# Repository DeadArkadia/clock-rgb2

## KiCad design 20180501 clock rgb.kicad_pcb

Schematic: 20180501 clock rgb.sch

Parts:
BT1: Battery CR2032; BatteryHolder_Keystone_1058_1x2032
C1, C2: 22pF; C_Rect_L4.0mm_W2.5mm_P2.50mm
C3: 1uF; C_Rect_L4.0mm_W2.5mm_P2.50mm
C4, C5, C7: 10uF; CP_Radial_D5.0mm_P2.50mm
C6, C8, C9: 1uF; CP_Radial_D5.0mm_P2.50mm
C10, C11, C12, C13: 0.1uF; CP_Radial_D5.0mm_P2.50mm
D1: APFA3010; LED_Avago_PLCC4_3.2x2.8mm_CW
D2, D3, D4, D5, D6, D7, D8, D9, D10, D11, D12, D13, D14, D15, D16, D17, D18, D19, D20, D21, D22, D23, D24, D25, D26, D27, D28, D29, D30, D31, D32, D33, D34, D35, D36, D37, D38, D39, D40, D41, D42, D43, D44, D45, D46, D47, D48, D49, D50, D51, D52, D53, D54, D55, D56, D57, D58, D59, D60, D61, D62, D63, D64, D65, D66, D67, D68, D69, D70, D71, D72, D73, D74, D75, D76, D77, D78, D79, D82, D83, D84, D85, D86, D87, D88, D91, D92, D93, D94, D95, D96, D97: LED_ARGB; LED_Avago_PLCC4_3.2x2.8mm_CW
D80, D81, D89, D90: LED; LED_D5.0mm
J1: Barrel_Jack; BARREL_JACK
J2: DB9M RS232; DSUB-9_Male_Horizontal_P2.77x2.84mm_EdgePinOffset7.70mm_Hou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
LS1: Speaker; Buzzer_15x7.5RM7.6
Q1, Q2, Q3: MMPQ2907A; SOIC-16_3.9x9.9mm_Pitch1.27mm
R1, R2, R4, R5, R7, R8, R10, R11, R13, R14, R16, R17, R19, R20, R23, R24, R26, R27, R29, R30, R32, R33, R35, R36, R38, R39, R41, R42, R51, R52, R54, R55, R57, R58, R60, R61, R63, R64, R66, R67, R69, R70, R81, R82, R84, R85, R87, R88, R90, R91, R93, R94, R96, R97, R99, R100, R111, R114, R117, R120, R123, R126, R129: 150; R_1210_3225Metric_Pad1.39x2.70mm_HandSolder
R3, R6, R9, R12, R15, R18, R21, R25, R28, R31, R34, R37, R40, R43, R53, R56, R59, R62, R65, R68, R71, R83, R86, R89, R92, R95, R98, R101: 300; R_1210_3225Metric_Pad1.39x2.70mm_HandSolder
R22: 100; R_Axial_DIN0207_L6.3mm_D2.5mm_P10.16mm_Horizontal
R44, R45, R47, R48, R49, R50, R72, R73, R74, R75, R76, R77, R78, R79, R80: 330; R_1210_3225Metric_Pad1.39x2.70mm_HandSolder
R46: 470; R_1210_3225Metric_Pad1.39x2.70mm_HandSolder
R102, R103: 2.2k; R_Axial_DIN0207_L6.3mm_D2.5mm_P10.16mm_Horizontal
R104: 10k; R_Axial_DIN0207_L6.3mm_D2.5mm_P10.16mm_Horizontal
R105, R106: 680; R_Axial_DIN0207_L6.3mm_D2.5mm_P10.16mm_Horizontal
R107, R108: 5k; R_Axial_DIN0207_L6.3mm_D2.5mm_P10.16mm_Horizontal
R109, R110, R132, R133: 10k; R_1210_3225Metric_Pad1.39x2.70mm_HandSolder
R112, R113, R115, R116, R118, R119, R121, R122, R124, R125, R127, R128, R130, R131: 100; R_1210_3225Metric_Pad1.39x2.70mm_HandSolder
RN1: 10k; R_Array_SIP4
RV1, RV2, RV3, RV4: 50k; Potentiometer_Alps_RK09K_Single_Vertical
SW1, SW2, SW3, SW4, SW5, SW6: SW_Push; SW_PUSH_6mm
U1: ATMEGA328P-PU; DIP-28_W7.62mm
U2, U3: 74164; DIP-14_W7.62mm
U5: LM7805_TO220; TO-220-3_Horizontal
U6, U7: PCA8856B; TSSOP-38_4.4x9.7mm_Pitch0.5mm
U8: DS3231-8; SOIC-8_3.9x4.9mm_Pitch1.27mm
U9: LM7812_TO220; TO-220-3_Horizontal
U10: MAX202; SOIC-16_3.9x9.9mm_Pitch1.27mm
Y1: 16MHz; Crystal_HC49-4H_Vertical

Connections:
+5V: C5.1, D89.2 (A), R102.2, R103.2, R104.2, R109.1, R110.1, RN1.1 (common), RV1.3, RV2.3, RV3.3, RV4.3, SW1.1, SW2.1, SW3.1, SW4.1, SW5.1, SW6.1, U1.7 (VCC), U1.20 (AVCC), U1.21 (AREF), U2.1 (A), U2.9 (~R), U2.14 (Vdd), U3.1 (A), U3.9 (~R), U3.14 (Vdd), U5.3 (VO), U6.2 (AD0), U6.38 (Vdd), U7.3 (AD1), U7.38 (Vdd), U8.2 (Vcc), U10.16 (VCC)
+12V: C7.1, D43.1, D44.1, D90.2 (A), Q1.10 (E4), Q1.12 (E3), Q1.14 (E2), Q1.16 (E1), Q2.10 (E4), Q2.12 (E3), Q2.14 (E2), Q3.10 (E4), Q3.12 (E3), Q3.14 (E2), Q3.16 (E1), U9.3 (VO)
/B: D1.4 (B), D2.4 (B), D3.4 (B), D4.4 (B), D5.4 (B), D6.4 (B), D7.4 (B), D8.4 (B), D9.4 (B), D10.4 (B), D11.4 (B), D12.4 (B), D13.4 (B), D14.4 (B), D15.4 (B), D16.4 (B), D17.4 (B), D18.4 (B), D19.4 (B), D20.4 (B), D21.4 (B), D22.4, D23.4, D24.4, D25.4, D26.4, D27.4, D28.4, D29.4, D30.4, D31.4, D32.4, D33.4, D34.4, D35.4, D36.4, D37.4, D38.4, D39.4, D40.4, D41.4, D42.4, D43.4, D44.4, D45.4, D46.4, D47.4, D48.4, D49.4, D50.4, D51.4, D52.4, D53.4, D54.4, D55.4, D56.4, D57.4, D58.4, D59.4, D60.4, D61.4, D62.4, D63.4, D64.4, D65.4, D66.4, D67.4, D68.4, D69.4, D70.4, D71.4, D72.4, D73.4, D74.4, D75.4, D76.4, D77.4, D78.4, D79.4, D82.4, D83.4, D84.4, D85.4, D86.4, D87.4, D88.4, R1.2, R4.2, R7.2, R10.2, R13.2, R16.2, R19.2, R23.2, R26.2, R29.2, R32.2, R35.2, R38.2, R41.2, R44.2, R51.2, R54.2, R57.2, R60.2, R63.2, R66.2, R69.2, R81.2, R84.2, R87.2, R90.2, R93.2, R96.2, R99.2
/B_COLON: R44.1, U7.33 (LED23)
/B_R1: R1.1, R23.1, R51.1, R81.1, U7.8 (LED2)
/B_R2: R4.1, R26.1, R54.1, R84.1, U7.11 (LED5)
/B_R3: R7.1, R29.1, R57.1, R87.1, U7.15 (LED8)
/B_R4: R10.1, R32.1, R60.1, R90.1, U7.19 (LED11)
/B_R5: R13.1, R35.1, R63.1, R93.1, U7.23 (LED14)
/B_R6: R16.1, R38.1, R66.1, R96.1, U7.27 (LED17)
/B_R7: R19.1, R41.1, R69.1, R99.1, U7.30 (LED20)
/DTR: C3.1, C6.1, C8.1, C9.1, U10.9 (R2OUT)
/DTR_PU: J2.4, R133.2, U10.8 (R2IN)
/G: D1.3 (G), D2.3 (G), D3.3 (G), D4.3 (G), D5.3 (G), D6.3 (G), D7.3 (G), D8.3 (G), D9.3 (G), D10.3 (G), D11.3 (G), D12.3 (G), D13.3 (G), D14.3 (G), D15.3 (G), D16.3 (G), D17.3 (G), D18.3 (G), D19.3 (G), D20.3 (G), D21.3 (G), D22.3, D23.3, D24.3, D25.3, D26.3, D27.3, D28.3, D29.3, D30.3, D31.3, D32.3, D33.3, D34.3, D35.3, D36.3, D37.3, D38.3, D39.3, D40.3, D41.3, D42.3, D43.3, D44.3, D45.3, D46.3, D47.3, D48.3, D49.3, D50.3, D51.3, D52.3, D53.3, D54.3, D55.3, D56.3, D57.3, D58.3, D59.3, D60.3, D61.3, D62.3, D63.3, D64.3, D65.3, D66.3, D67.3, D68.3, D69.3, D70.3, D71.3, D72.3, D73.3, D74.3, D75.3, D76.3, D77.3, D78.3, D79.3, D82.3, D83.3, D84.3, D85.3, D86.3, D87.3, D88.3, R2.2, R5.2, R8.2, R11.2, R14.2, R17.2, R20.2, R24.2, R27.2, R30.2, R33.2, R36.2, R39.2, R42.2, R45.2, R52.2, R55.2, R58.2, R61.2, R64.2, R67.2, R70.2, R82.2, R85.2, R88.2, R91.2, R94.2, R97.2, R100.2
/G_COLON: R45.1, U7.32 (LED22)
/G_R1: R2.1, R24.1, R52.1, R82.1, U7.7 (LED1)
/G_R2: R5.1, R27.1, R55.1, R85.1, U7.10 (LED4)
/G_R3: R8.1, R30.1, R58.1, R88.1, U7.13 (LED7)
/G_R4: R11.1, R33.1, R61.1, R91.1, U7.17 (LED10)
/G_R5: R14.1, R36.1, R64.1, R94.1, U7.22 (LED13)
/G_R6: R17.1, R39.1, R67.1, R97.1, U7.26 (LED16)
/G_R7: R20.1, R42.1, R70.1, R100.1, U7.29 (LED19)
/OE: RN1.4 (R3), U1.12 ((PCINT22/OC0A/AIN0)PD6), U6.5 (OE), U7.5 (OE)
/RXD: R80.1, U1.3 ((PCINT17/TXD)PD1), U10.11 (T1IN)
/R_COLON: R46.1, U7.31 (LED21)
/R_R1: R3.1, R25.1, R53.1, R83.1, U7.6 (LED0)
/R_R2: R6.1, R28.1, R56.1, R86.1, U7.9 (LED3)
/R_R3: R9.1, R31.1, R59.1, R89.1, U7.12 (LED6)
/R_R4: R12.1, R34.1, R62.1, R92.1, U7.16 (LED9)
/R_R5: R15.1, R37.1, R65.1, R95.1, U7.20 (LED12)
/R_R6: R18.1, R40.1, R68.1, R98.1, U7.24 (LED15)
/R_R7: R21.1, R43.1, R71.1, R101.1, U7.28 (LED18)
/SCL: RN1.2 (R1), U1.27 ((PCINT12/SDA/ADC4)PC4), U6.36 (SCL), U7.36 (SCL), U8.8 (SCL)
/SDA: RN1.3 (R2), U1.28 ((PCINT13/SCL/ADC5)PC5), U6.37 (SDA), U7.37 (SDA), U8.7 (SDA)
/STATUS1_B: R113.2, U6.8 (LED2)
/STATUS1_G: R112.2, U6.7 (LED1)
/STATUS1_R: R111.2, U6.6 (LED0)
/STATUS2_B: R116.2, U6.11 (LED5)
/STATUS2_G: R115.2, U6.10 (LED4)
/STATUS2_R: R114.2, U6.9 (LED3)
/STATUS3_B: R119.2, U6.15 (LED8)
/STATUS3_G: R118.2, U6.13 (LED7)
/STATUS3_R: R117.2, U6.12 (LED6)
/STATUS4_B: R122.2, U6.19 (LED11)
/STATUS4_G: R121.2, U6.17 (LED10)
/STATUS4_R: R120.2, U6.16 (LED9)
/STATUS5_B: R125.2, U6.23 (LED14)
/STATUS5_G: R124.2, U6.22 (LED13)
/STATUS5_R: R123.2, U6.20 (LED12)
/STATUS6_B: R128.2, U6.27 (LED17)
/STATUS6_G: R127.2, U6.26 (LED16)
/STATUS6_R: R126.2, U6.24 (LED15)
/STATUS7_B: R131.2, U6.30 (LED20)
/STATUS7_G: R130.2, U6.29 (LED19)
/STATUS7_R: R129.2, U6.28 (LED18)
/TXD: R79.1, U1.2 ((PCINT16/RXD)PD0), U10.12 (R1OUT)
/TXD_PU: J2.2, R132.2, U10.13 (R1IN)
Earth: BT1.2 (-), C1.2, C2.2, C4.2, C5.2, C7.2, C12.2, C13.1, D80.1 (K), D81.1 (K), J1.2, J1.3, J2.0 (PAD), J2.5, LS1.1, R107.1, R108.1, R132.1, R133.1, RV1.1, RV2.1, RV3.1, RV4.1, U1.8 (GND), U1.22 (GND), U2.7 (Vss), U3.7 (Vss), U5.2 (GND), U6.3 (AD1), U6.4 (AD2), U6.14 (Vss), U6.18 (Vss), U6.21 (Vss), U6.25 (Vss), U6.34 (Vss), U7.2 (AD0), U7.4 (AD2), U7.14 (Vss), U7.18 (Vss), U7.21 (Vss), U7.25 (Vss), U7.34 (Vss), U8.5 (GND), U9.2 (GND), U10.15 (GND)
unnamed: BT1.1 (+), U8.6 (VBat)
unnamed: C1.1, U1.9 ((PCINT6/XTAL1/TOSC1)PB6), Y1.1
unnamed: C2.1, U1.10 ((PCINT7/XTAL2/TOSC2)PB7), Y1.2
unnamed: C3.2, U1.1 ((PCINT14/~RESET~)PC6)
unnamed: C6.2, R104.1, U8.4 (RST)
unnamed: C8.2, R109.2, U6.35 (RESET)
unnamed: C9.2, R110.2, U7.35 (RESET)
unnamed: C10.1, U10.1 (C1+)
unnamed: C10.2, U10.3 (C1-)
unnamed: C11.1, U10.4 (C2+)
unnamed: C11.2, U10.5 (C2-)
unnamed: C12.1, U10.2 (VS+)
unnamed: C13.2, U10.6 (VS-)
unnamed: D22.1, D23.1, D24.1, D25.1, D26.1, D27.1, D28.1, D29.1, D30.1, D31.1, D32.1, D33.1, D34.1, D35.1, D36.1, D37.1, D38.1, D39.1, D40.1, D41.1, D42.1, Q1.3 (C2), Q1.4 (C2)
unnamed: D45.1, D46.1, D47.1, D48.1, D49.1, D50.1, D51.1, D52.1, D53.1, D54.1, D55.1, D56.1, D57.1, D58.1, D59.1, D60.1, D61.1, D62.1, D63.1, D64.1, D65.1, Q1.5 (C3), Q1.6 (C3)
unnamed: D66.1, D67.1, D68.1, D69.1, D70.1, D71.1, D72.1, D73.1, D74.1, D75.1, D76.1, D77.1, D78.1, D79.1, D82.1, D83.1, D84.1, D85.1, D86.1, D87.1, D88.1, Q1.7 (C4), Q1.8 (C4)
unnamed: D80.2 (A), R79.2
unnamed: D81.2 (A), R80.2
unnamed: D89.1 (K), R107.2
unnamed: D90.1 (K), R108.2
unnamed: D91.1, Q2.3 (C2), Q2.4 (C2)
unnamed: D91.2, R111.1
unnamed: D91.3, R112.1
unnamed: D91.4, R113.1
unnamed: D92.1, Q2.5 (C3), Q2.6 (C3)
unnamed: D92.2, R114.1
unnamed: D92.3, R115.1
unnamed: D92.4, R116.1
unnamed: D93.1, Q2.7 (C4), Q2.8 (C4)
unnamed: D93.2, R117.1
unnamed: D93.3, R118.1
unnamed: D93.4, R119.1
unnamed: D94.1, Q3.1 (C1), Q3.2 (C1)
unnamed: D94.2, R120.1
unnamed: D94.3, R121.1
unnamed: D94.4, R122.1
unnamed: D95.1, Q3.3 (C2), Q3.4 (C2)
unnamed: D95.2, R123.1
unnamed: D95.3, R124.1
unnamed: D95.4, R125.1
unnamed: D96.1, Q3.5 (C3), Q3.6 (C3)
unnamed: D96.2, R126.1
unnamed: D96.3, R127.1
unnamed: D96.4, R128.1
unnamed: D97.1, Q3.7 (C4), Q3.8 (C4)
unnamed: D97.2, R129.1
unnamed: D97.3, R130.1
unnamed: D97.4, R131.1
unnamed: J2.3, U10.14 (T1OUT)
unnamed: LS1.2, R22.2
unnamed: Q1.9 (B3), R50.2
unnamed: Q1.11 (B3), R49.2
unnamed: Q1.13 (B2), R48.2
unnamed: Q1.15 (B1), R47.2
unnamed: Q2.9 (B3), R76.1
unnamed: Q2.11 (B3), R77.1
unnamed: Q2.13 (B2), R78.1
unnamed: Q3.9 (B3), R72.1
unnamed: Q3.11 (B3), R73.1
unnamed: Q3.13 (B2), R74.1
unnamed: Q3.15 (B1), R75.1
unnamed: R22.1, U1.17 ((PCINT3/OC2A/MOSI)PB3)
unnamed: R47.1, U2.6 (Qd)
unnamed: R48.1, U2.5 (Qc)
unnamed: R49.1, U2.4 (Qb)
unnamed: R50.1, U2.3 (Qa)
unnamed: R72.2, U3.3 (Qa)
unnamed: R73.2, U3.4 (Qb)
unnamed: R74.2, U3.5 (Qc)
unnamed: R75.2, U3.6 (Qd)
unnamed: R76.2, U3.10 (Qe)
unnamed: R77.2, U3.11 (Qf)
unnamed: R78.2, U3.12 (Qg)
unnamed: R102.1, R105.2
unnamed: R103.1, R106.2
unnamed: R105.1, U6.1 (REXT)
unnamed: R106.1, U7.1 (REXT)
unnamed: RV1.2, U1.23 ((PCINT8/ADC0)PC0)
unnamed: RV2.2, U1.24 ((PCINT9/ADC1)PC1)
unnamed: RV3.2, U1.25 ((PCINT10/ADC2)PC2)
unnamed: RV4.2, U1.26 ((PCINT11/ADC3)PC3)
unnamed: SW1.2, U1.18 ((PCINT4/MISO)PB4)
unnamed: SW2.2, U1.19 ((PCINT5/SCK)PB5)
unnamed: SW3.2, U1.4 ((PCINT18/INT0)PD2)
unnamed: SW4.2, U1.5 ((PCINT19/OC2B/INT1)PD3)
unnamed: SW5.2, U1.6 ((PCINT20/XCK/T0)PD4)
unnamed: SW6.2, U1.11 ((PCINT21/OC0B/T1)PD5)
unnamed: U1.14 ((PCINT0/CLKO/ICP1)PB0), U2.2 (B)
unnamed: U1.15 ((PCINT1/OC1A)PB1), U2.8 (CK), U3.8 (CK)
unnamed: U1.16 ((PCINT2/OC1B/~SS~)PB2), U3.2 (B)
VCC: C4.1, J1.1, U5.1 (VI), U9.1 (VI)

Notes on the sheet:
110 1000 (68h)
001 0101 (2Ah)
000 0101 (0Ah)
TX/RX relative to PC

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
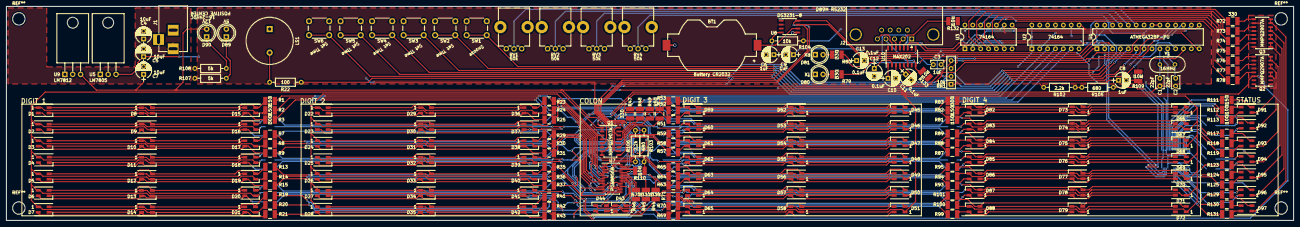
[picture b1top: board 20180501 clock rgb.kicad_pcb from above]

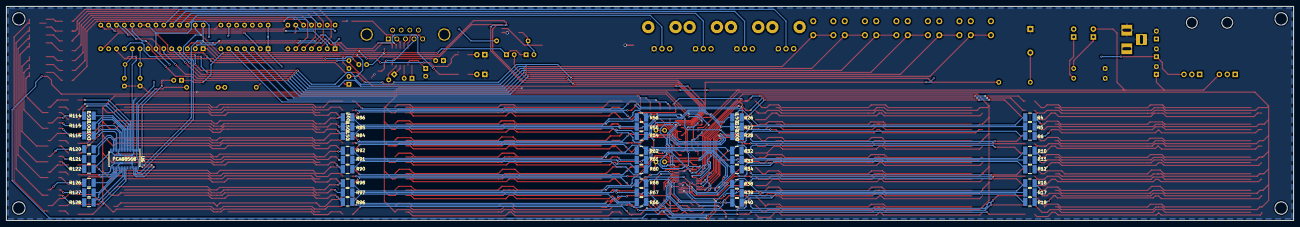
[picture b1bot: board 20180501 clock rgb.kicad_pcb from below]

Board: 2 copper layers, 415.0 x 69.0 mm, 271 parts (46 on the bottom side), 151 nets.

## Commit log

2018-05-09 github is killing me
2018-05-09 asdf
    asd
